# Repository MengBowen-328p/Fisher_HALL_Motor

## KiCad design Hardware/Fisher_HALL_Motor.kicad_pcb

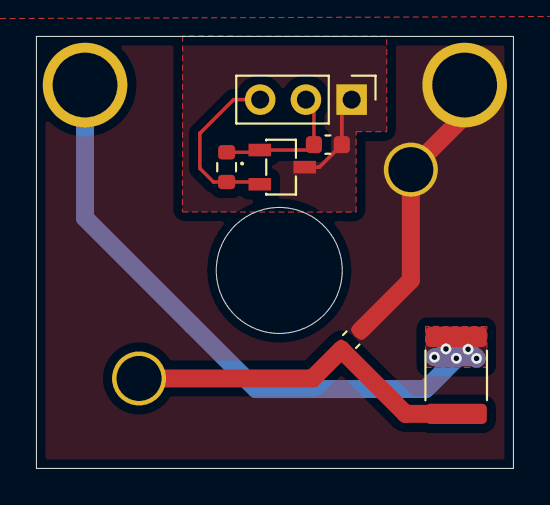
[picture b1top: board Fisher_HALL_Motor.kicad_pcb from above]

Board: 2 copper layers, 26.5 x 24.0 mm, 10 parts (0 on the bottom side), 6 nets.

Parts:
C1, C2: 0.1uF; C_0603_1608Metric
F1: 9V3A; R_1812_4532Metric
J1: 9V_IN; 3mm_Banana_Socket
J2: Power_GND; 3mm_Banana_Socket
J3: MOTOR+; Motor_Conn
J4: MOTOR-; Motor_Conn
J5: Conn_01x03_Pin; PinHeader_1x03_P2.54mm_Vertical
R1: 100K; R_0603_1608Metric
U1: A3144E-JSM; SOT-23-3_L2.9-W1.6-P1.90-LS2.8-BR-CW

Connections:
+3.3V: C2.1, J5.2, R1.1, U1.1 (VSUP)
/SIGNAL: J5.3, R1.2, U1.3 (VOUT)
GND: C2.2, J5.1, U1.2 (GND)
GNDPWR: C1.2, J2.1, J4.1
unnamed: F1.1, J1.1
unnamed: C1.1, F1.2, J3.1

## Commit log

2024-03-14 Finished PCB
